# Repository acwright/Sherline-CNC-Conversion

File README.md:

# Sherline CNC Conversion

Project files for my Sherline Lathe and Mill CNC Conversion

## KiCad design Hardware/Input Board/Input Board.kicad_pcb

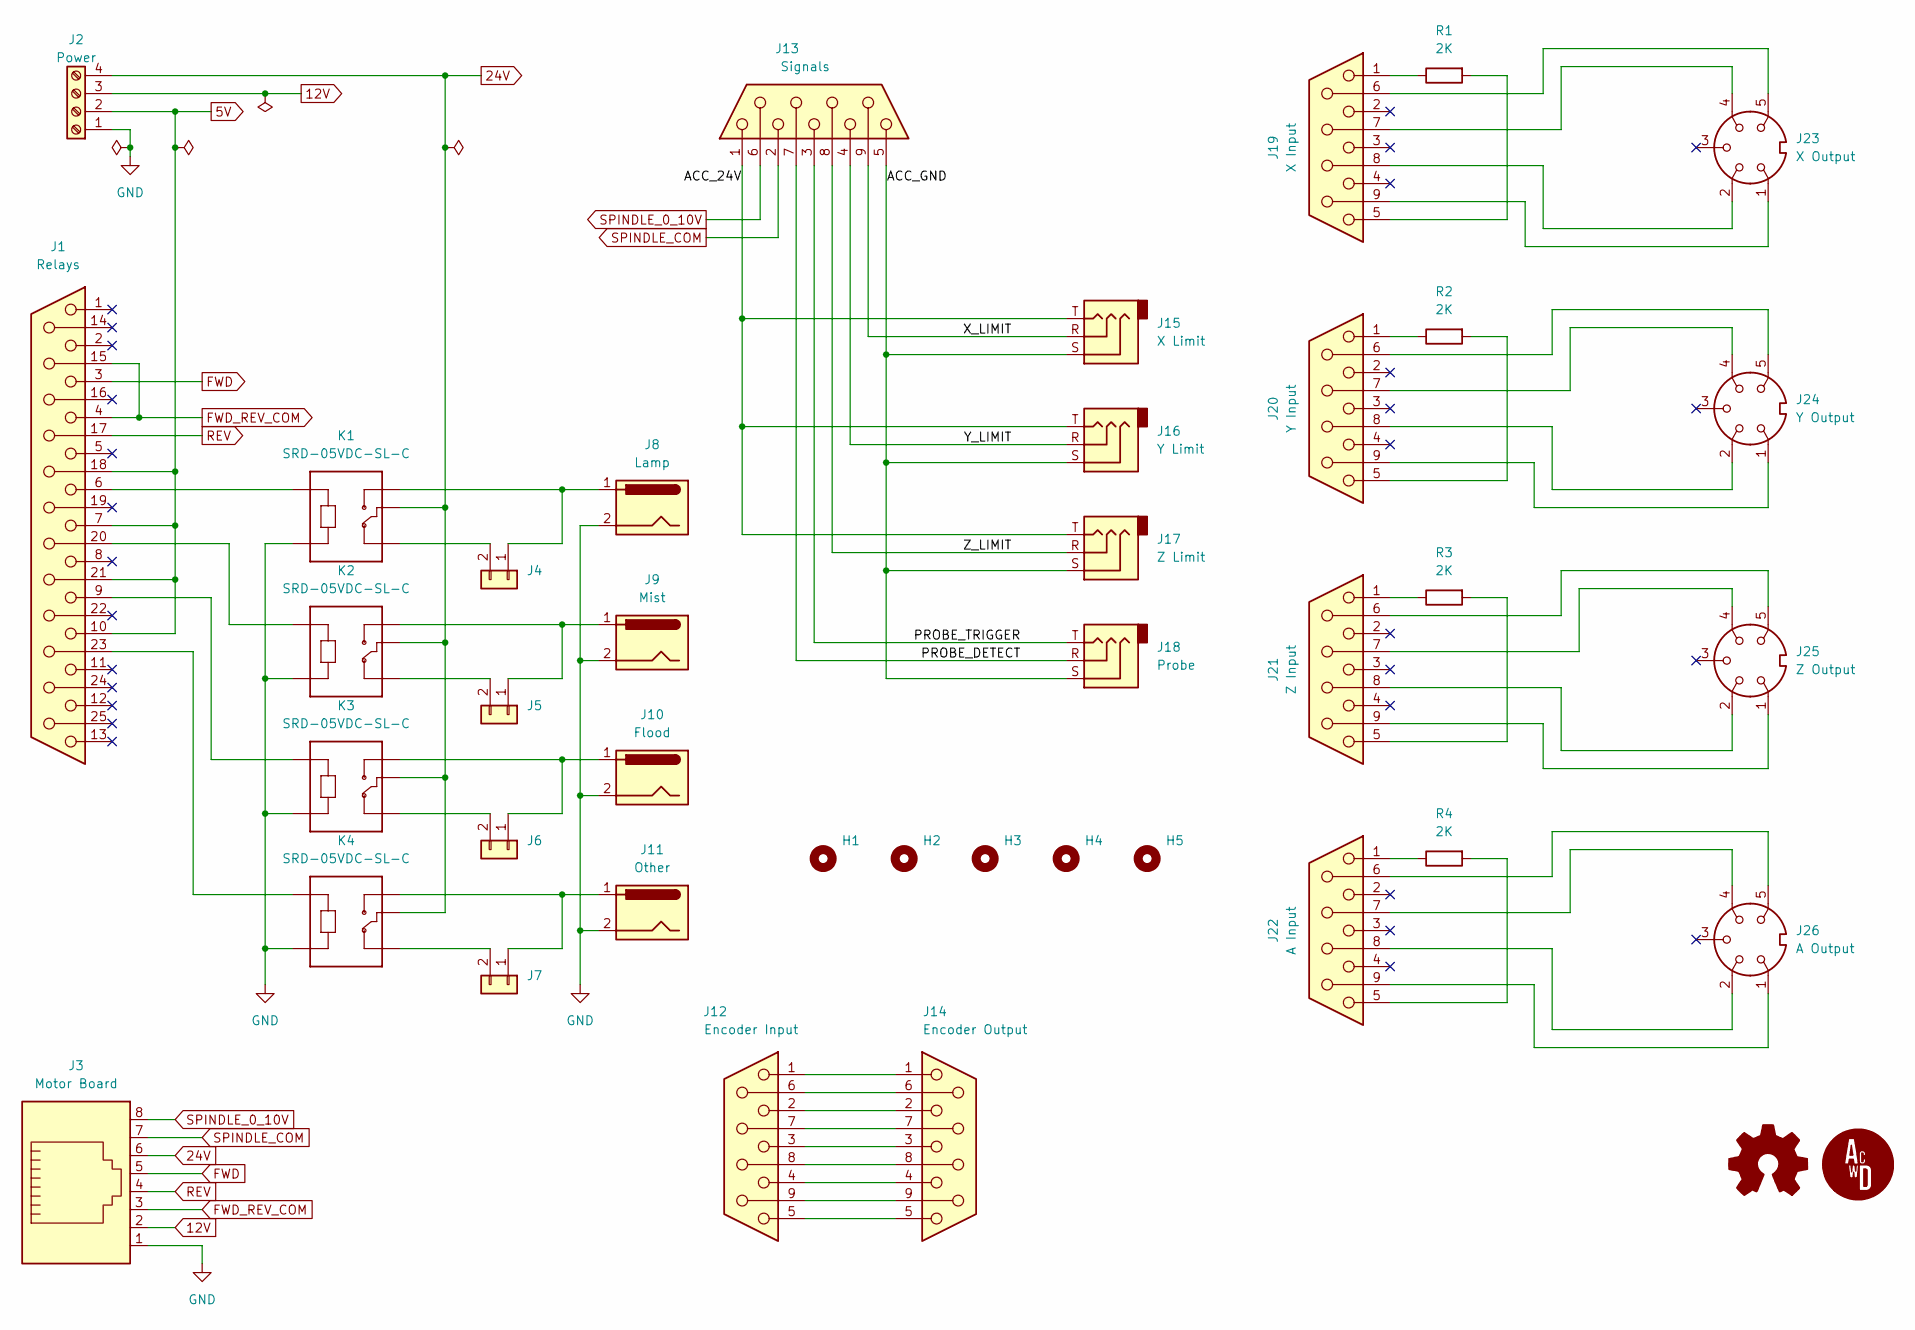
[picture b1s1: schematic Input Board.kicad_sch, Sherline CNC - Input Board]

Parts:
H1, H2, H3, H4, H5: MountingHole_Pad; MountingHole_3.2mm_M3
J1: Relays; DSUB-25_Female_Vertical_P2.77x2.84mm_MountingHoles
J2: Power; TerminalBlock_Phoenix_PT-1,5-4-5.0-H_1x04_P5.00mm_Horizontal
J3: Motor Board; RJ45_Amphenol_54602-x08_Horizontal
J4, J5, J6, J7: Conn_01x02; PinHeader_1x02_P2.54mm_Vertical
J8: Lamp; BarrelJack_Horizontal
J9: Mist; BarrelJack_Horizontal
J10: Flood; BarrelJack_Horizontal
J11: Other; BarrelJack_Horizontal
J12: Encoder Input; DSUB-9_Female_Vertical_P2.77x2.84mm_MountingHoles
J13: Signals; DSUB-9_Female_Vertical_P2.77x2.84mm_MountingHoles
J14: Encoder Output; DSUB-9_Female_Horizontal_P2.77x2.84mm_EdgePinOffset9.90mm_H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
J15: X Limit; PJ-307-3
J16: Y Limit; PJ-307-3
J17: Z Limit; PJ-307-3
J18: Probe; PJ-307-3
J19: X Input; DSUB-9_Female_Vertical_P2.77x2.84mm_MountingHoles
J20: Y Input; DSUB-9_Female_Vertical_P2.77x2.84mm_MountingHoles
J21: Z Input; DSUB-9_Female_Vertical_P2.77x2.84mm_MountingHoles
J22: A Input; DSUB-9_Female_Vertical_P2.77x2.84mm_MountingHoles
J23: X Output; DIN5-RA-PTH
J24: Y Output; DIN5-RA-PTH
J25: Z Output; DIN5-RA-PTH
J26: A Output; DIN5-RA-PTH
K1, K2, K3, K4: SRD-05VDC-SL-C
R1, R2, R3, R4: 2K; R_Axial_DIN0411_L9.9mm_D3.6mm_P15.24mm_Horizontal

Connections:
5V: J1.7, J1.10, J1.18, J1.21, J2.2
12V: J2.3, J3.2
24V: J2.4, J3.6, K1.COM, K2.COM, K3.COM, K4.COM
/ACC_24V: J13.1, J15.T, J16.T, J17.T
/ACC_GND: J13.5, J15.S, J16.S, J17.S, J18.S
/PROBE_DETECT: J13.7, J18.R
/PROBE_TRIGGER: J13.3, J18.T
/X_LIMIT: J13.9, J15.R
/Y_LIMIT: J13.4, J16.R
/Z_LIMIT: J13.8, J17.R
FWD: J1.3, J3.5
FWD_REV_COM: J1.4, J1.15, J3.3
GND: J2.1, J3.1, J8.2, J9.2, J10.2, J11.2, K1.A2, K2.A2, K3.A2, K4.A2
unnamed: J1.6, K1.A1
unnamed: J1.9, K3.A1
unnamed: J1.20, K2.A1
unnamed: J1.23, K4.A1
unnamed: J4.1, J8.1, K1.NO
unnamed: J4.2, K1.NC
unnamed: J5.1, J9.1, K2.NO
unnamed: J5.2, K2.NC
unnamed: J6.2, K3.NC
unnamed: J7.2, K4.NC
unnamed: J6.1, J10.1, K3.NO
unnamed: J7.1, J11.1, K4.NO
unnamed: J12.1, J14.1
unnamed: J12.2, J14.2
unnamed: J12.3, J14.3
unnamed: J12.4, J14.4
unnamed: J12.5, J14.5
unnamed: J12.6, J14.6
unnamed: J12.7, J14.7
unnamed: J12.8, J14.8
unnamed: J12.9, J14.9
unnamed: J19.1, R1.1
unnamed: J19.5, R1.2
unnamed: J19.6, J23.5
unnamed: J19.7, J23.4
unnamed: J19.8, J23.2
unnamed: J19.9, J23.1
unnamed: J20.1, R2.1
unnamed: J20.5, R2.2
unnamed: J20.6, J24.5
unnamed: J20.7, J24.4
unnamed: J20.8, J24.2
unnamed: J20.9, J24.1
unnamed: J21.1, R3.1
unnamed: J21.5, R3.2
unnamed: J21.6, J25.5
unnamed: J21.7, J25.4
unnamed: J21.8, J25.2
unnamed: J21.9, J25.1
unnamed: J22.1, R4.1
unnamed: J22.5, R4.2
unnamed: J22.6, J26.5
unnamed: J22.7, J26.4
unnamed: J22.8, J26.2
unnamed: J22.9, J26.1
REV: J1.17, J3.4
SPINDLE_0_10V: J3.8, J13.6
SPINDLE_COM: J3.7, J13.2

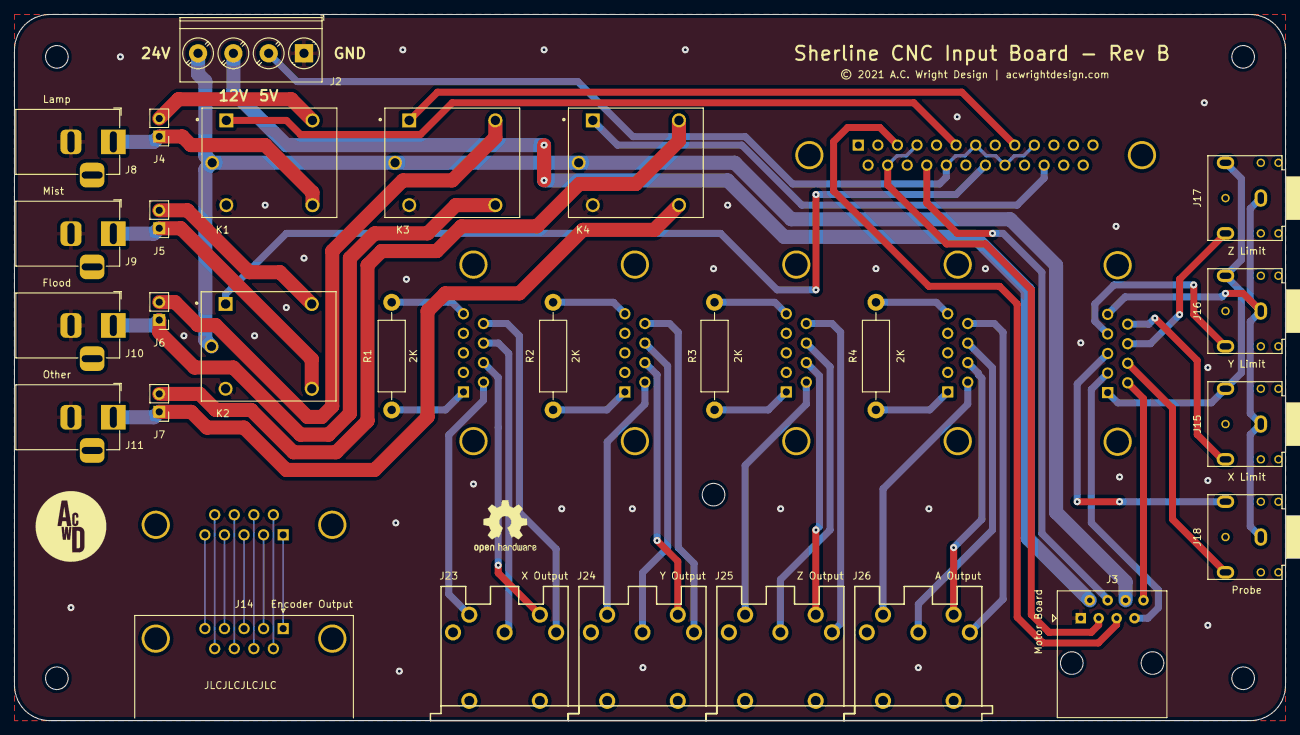
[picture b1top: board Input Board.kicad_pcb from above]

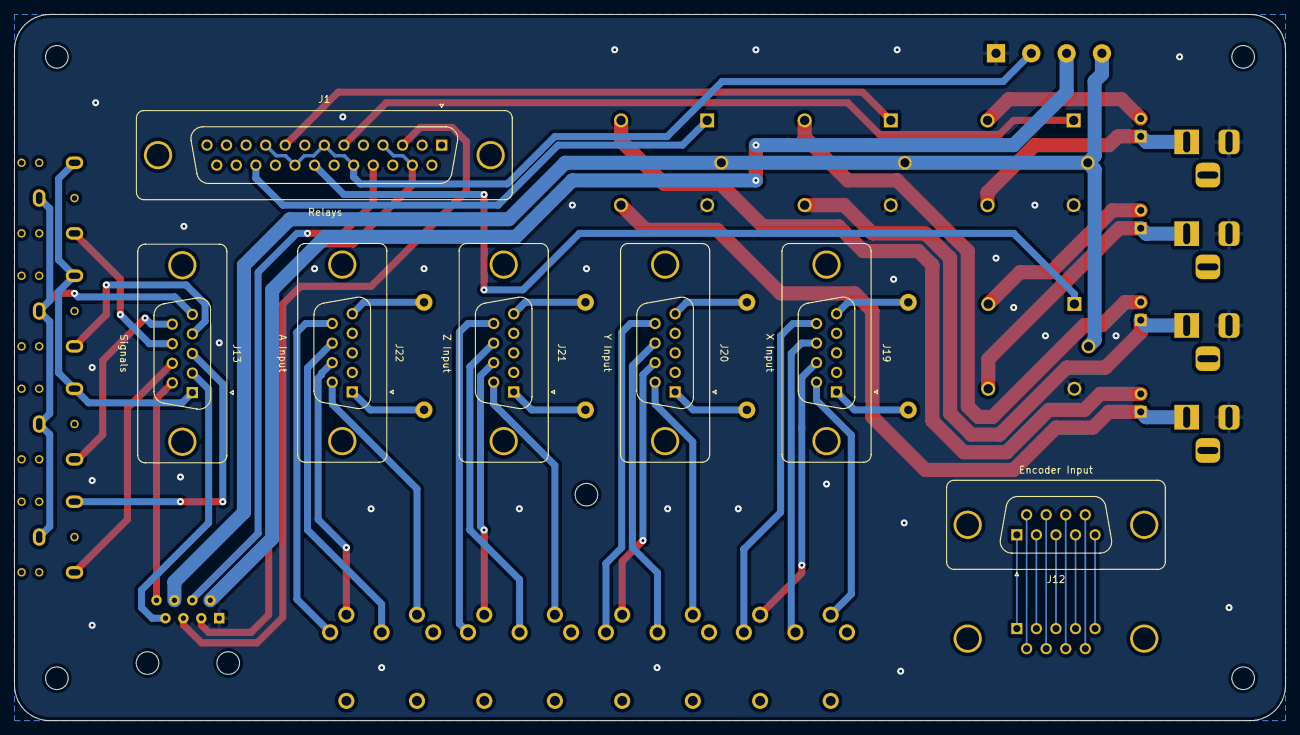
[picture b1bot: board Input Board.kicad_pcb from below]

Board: 2 copper layers, 180.0 x 100.0 mm, 39 parts (7 on the bottom side), 61 nets.

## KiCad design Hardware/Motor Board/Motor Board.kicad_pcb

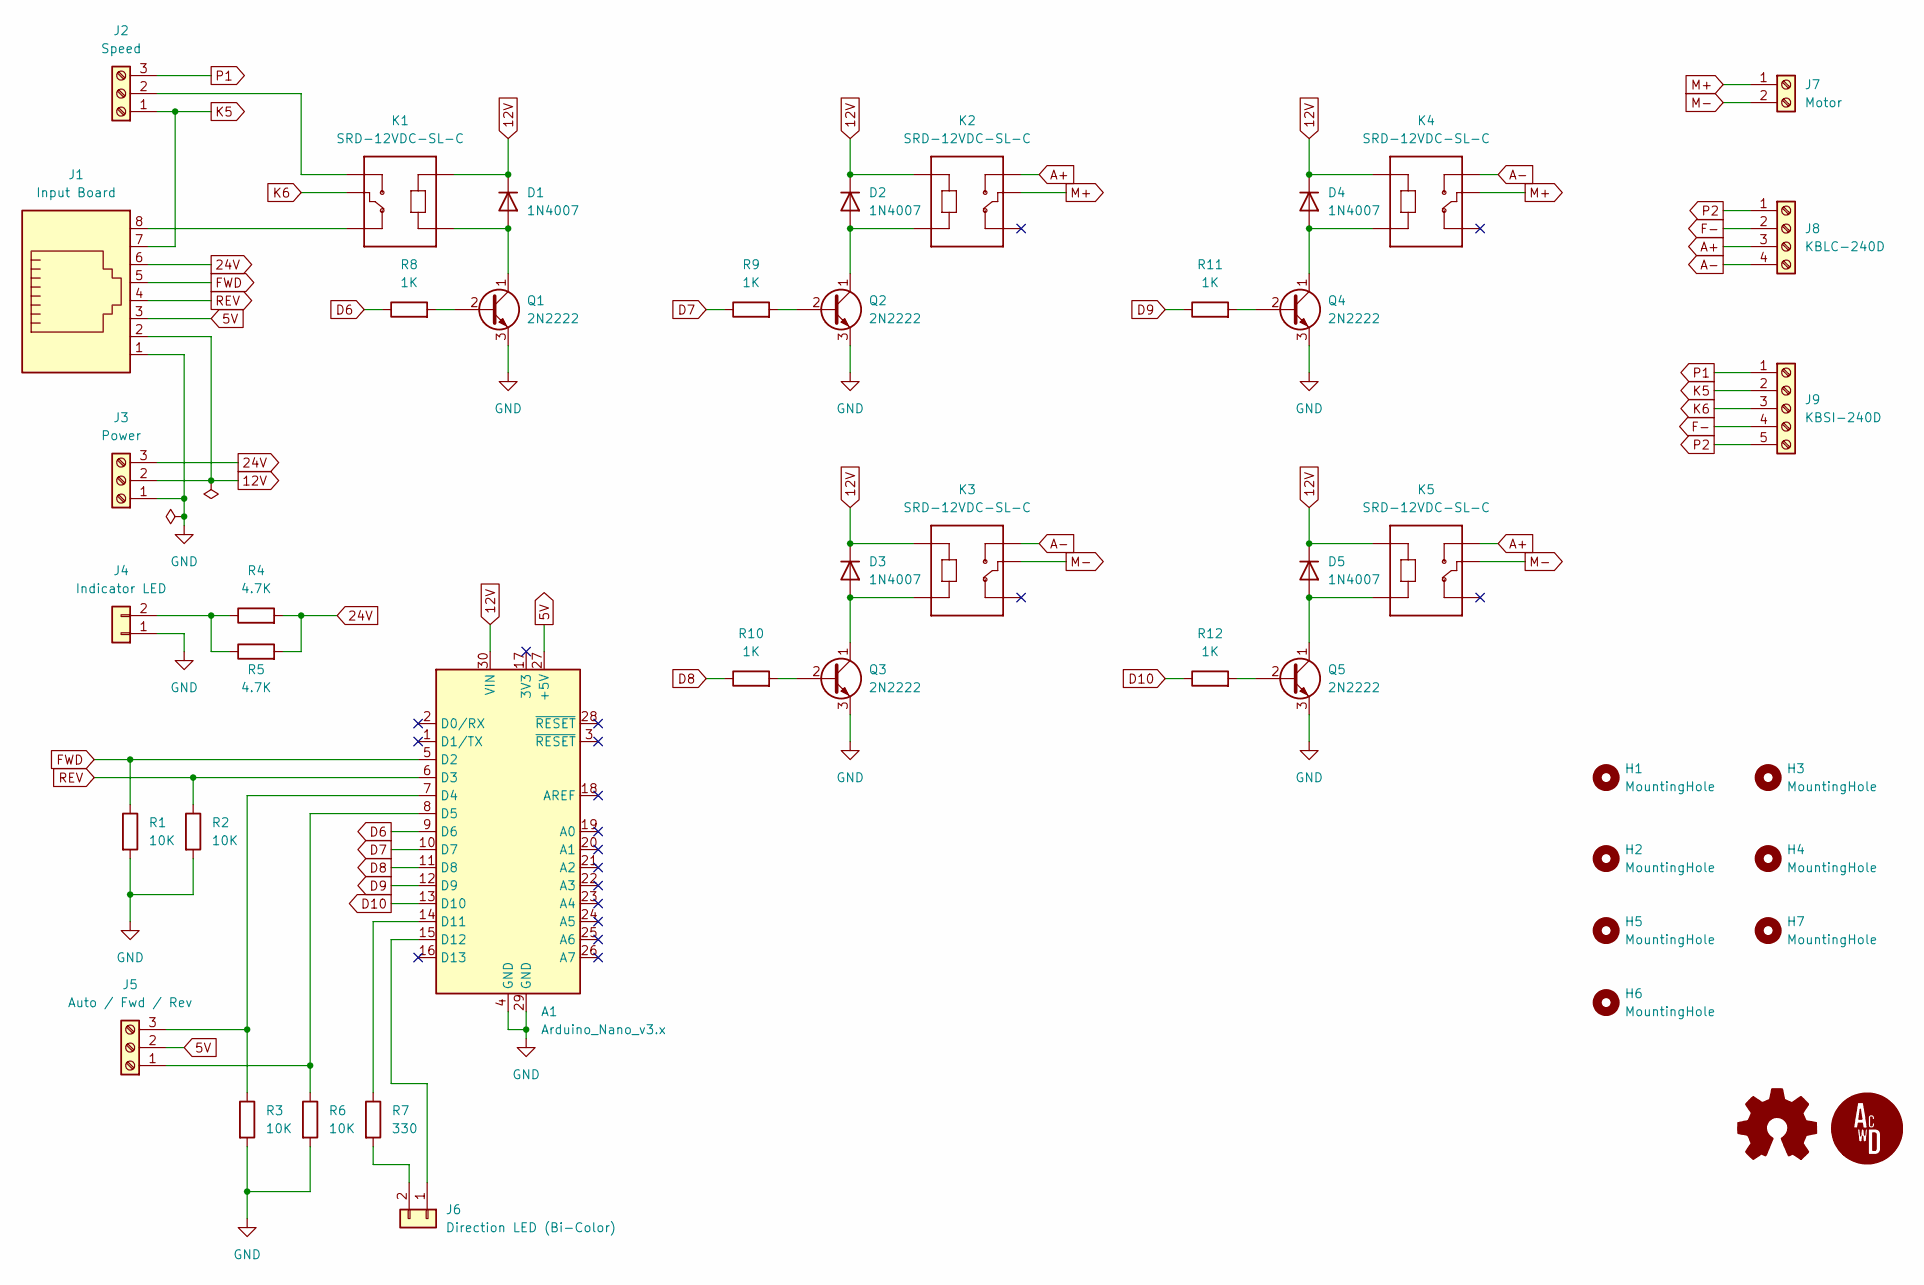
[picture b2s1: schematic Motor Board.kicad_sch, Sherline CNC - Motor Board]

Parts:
A1: Arduino_Nano_v3.x; Arduino_Nano
D1, D2, D3, D4, D5: 1N4007; D_DO-41_SOD81_P10.16mm_Horizontal
H1, H2, H3, H4, H5, H6, H7: MountingHole; MountingHole_3.2mm_M3
J1: Input Board; RJ45_Amphenol_54602-x08_Horizontal
J2: Speed; TerminalBlock_Phoenix_PT-1,5-3-5.0-H_1x03_P5.00mm_Horizontal
J3: Power; TerminalBlock_Phoenix_PT-1,5-3-5.0-H_1x03_P5.00mm_Horizontal
J4: Indicator LED; PinHeader_1x02_P2.54mm_Vertical
J5: Auto / Fwd / Rev; TerminalBlock_Phoenix_PT-1,5-3-5.0-H_1x03_P5.00mm_Horizontal
J6: Direction LED (Bi-Color); PinHeader_1x02_P2.54mm_Vertical
J7: Motor; TerminalBlock_Phoenix_PT-1,5-2-5.0-H_1x02_P5.00mm_Horizontal
J8: KBLC-240D; TerminalBlock_Phoenix_PT-1,5-4-5.0-H_1x04_P5.00mm_Horizontal
J9: KBSI-240D; TerminalBlock_Phoenix_PT-1,5-5-5.0-H_1x05_P5.00mm_Horizontal
K1, K2, K3, K4, K5: SRD-12VDC-SL-C; SRD-05VDC-SL-C
Q1, Q2, Q3, Q4, Q5: 2N2222; TO-92L_HandSolder
R1, R2, R3, R6: 10K; R_Axial_DIN0309_L9.0mm_D3.2mm_P12.70mm_Horizontal
R4, R5: 4.7K; R_Axial_DIN0309_L9.0mm_D3.2mm_P12.70mm_Horizontal
R7: 330; R_Axial_DIN0309_L9.0mm_D3.2mm_P12.70mm_Horizontal
R8, R9, R10, R11, R12: 1K; R_Axial_DIN0309_L9.0mm_D3.2mm_P12.70mm_Horizontal

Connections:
5V: A1.27 (+5V), J1.3, J5.2
12V: A1.30 (VIN), D1.1 (K), D2.1 (K), D3.1 (K), D4.1 (K), D5.1 (K), J1.2, J3.2, K1.A1, K2.A1, K3.A1, K4.A1, K5.A1
24V: J1.6, J3.3, R4.2, R5.2
A+: J8.3, K2.NO, K5.NO
A-: J8.4, K3.NO, K4.NO
D6: A1.9 (D6), R8.1
D7: A1.10 (D7), R9.1
D8: A1.11 (D8), R10.1
D9: A1.12 (D9), R11.1
D10: A1.13 (D10), R12.1
F-: J8.2, J9.4
FWD: A1.5 (D2), J1.5, R1.1
GND: A1.4 (GND), A1.29 (GND), J1.1, J3.1, J4.1, Q1.3 (E), Q2.3 (E), Q3.3 (E), Q4.3 (E), Q5.3 (E), R1.2, R2.2, R3.2, R6.2
K5: J1.7, J2.1, J9.2
K6: J9.3, K1.COM
M+: J7.1, K2.COM, K4.COM
M-: J7.2, K3.COM, K5.COM
unnamed: A1.7 (D4), J5.3, R3.1
unnamed: A1.8 (D5), J5.1, R6.1
unnamed: A1.14 (D11), R7.1
unnamed: A1.15 (D12), J6.1
unnamed: D1.2 (A), K1.A2, Q1.1 (C)
unnamed: D2.2 (A), K2.A2, Q2.1 (C)
unnamed: D3.2 (A), K3.A2, Q3.1 (C)
unnamed: D4.2 (A), K4.A2, Q4.1 (C)
unnamed: D5.2 (A), K5.A2, Q5.1 (C)
unnamed: J1.8, K1.NC
unnamed: J2.2, K1.NO
unnamed: J4.2, R4.1, R5.1
unnamed: J6.2, R7.2
unnamed: Q1.2 (B), R8.2
unnamed: Q2.2 (B), R9.2
unnamed: Q3.2 (B), R10.2
unnamed: Q4.2 (B), R11.2
unnamed: Q5.2 (B), R12.2
P1: J2.3, J9.1
P2: J8.1, J9.5
REV: A1.6 (D3), J1.4, R2.1

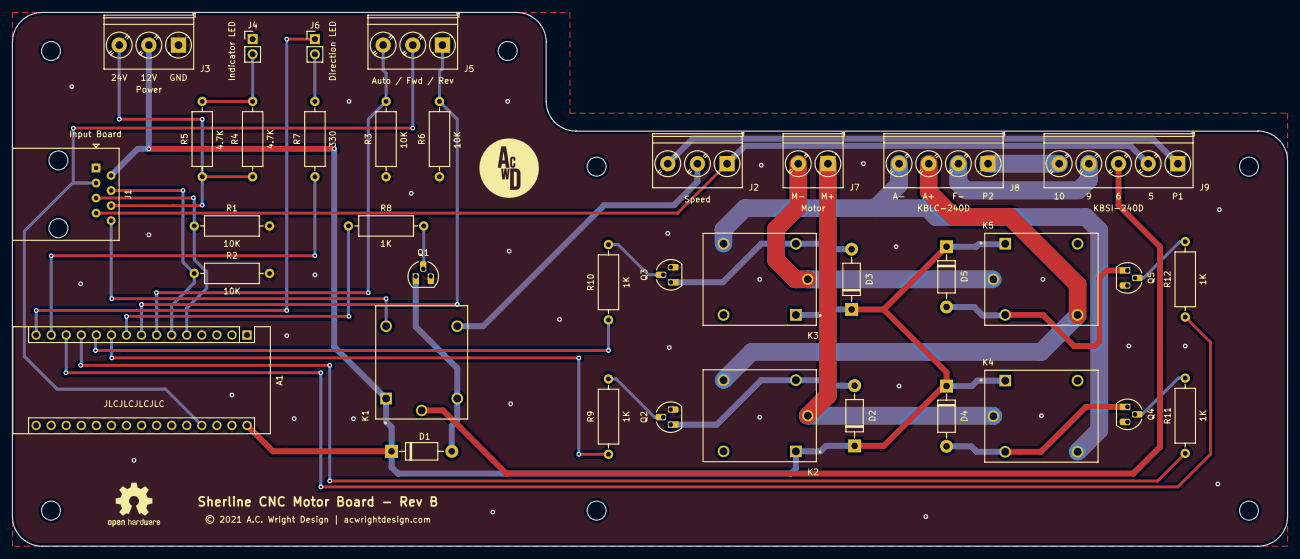
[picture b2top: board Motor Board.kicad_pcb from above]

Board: 2 copper layers, 215.0 x 90.0 mm, 44 parts (0 on the bottom side), 38 nets.

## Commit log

2021-11-29 Working on schematics
2021-12-02 Library cleanup
2021-12-04 Finish schematics
2021-12-04 Add missing footprints
2021-12-06 Input board complete
2021-12-08 Rev A boards ordered
2022-02-11 Add Rev B

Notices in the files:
Hardware/Input Board/Input Board.kicad_pcb:
© 2021 A.C. Wright Design | acwrightdesign.com
